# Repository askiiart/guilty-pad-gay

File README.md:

# GUILTY PAD -GAY-

Look this was gonna be normal but then the woke left made me add yuri

---

This is a macro pad which is designed with the [Guilty Pad XX Accent Core Plus Yuri](https://github.com/askiiart/guilty-pad-xx-accent-core-plus-yuri) in mind - can either act independently, or with the right firmware, could theoretically act as a very weird split keyboard. If you wanna get really crazy, it even has exposed i2c for expandability. For now it just includes very basic kmk firmware for testing.

## Bill of Materials

|Name                 |Quantity needed|MOQ|Price |Quantity to order|Link                                                           |Total   |
|---------------------|---------------|---|------|-----------------|---------------------------------------------------------------|--------|
|Xiao nRF52840        |1              |1  |9.99  |1                |<https://www.seeedstudio.com/Seeed-XIAO-BLE-nRF52840-p-5201.html>|9.99    |
|903090 lipo          |1              |1  |11.69 |1                |<https://www.aliexpress.us/item/3256809116041100.html>           |11.69   |
|AO3400A              |1              |20 |0.0214|20               |<https://www.lcsc.com/product-detail/C49195711.html>             |0.428   |
|AO3401A              |1              |20 |0.0321|20               |<https://www.lcsc.com/product-detail/C347476.html>               |0.642   |
|1N5819WS             |8              |100|0.0107|100              |<https://www.lcsc.com/product-detail/C191023.html>               |1.07    |
|74LV1T08GW-TP        |1              |10 |0.0609|10               |<https://www.lcsc.com/product-detail/C42460230.html>             |0.609   |
|TPS613222ADBVR       |1              |5  |0.1574|5                |<https://www.lcsc.com/product-detail/C2071163.html>              |0.787   |
|Inductor             |1              |5  |0.1508|5                |<https://www.lcsc.com/product-detail/C17701271.html>             |0.754   |
|SK6803MINI-E         |6              |10 |0.085 |10               |<https://www.lcsc.com/product-detail/C5242955.html>              |0.85    |
|22uF cap             |1              |20 |0.0354|20               |<https://www.lcsc.com/product-detail/C577040.html>               |0.708   |
|2M resistor          |1              |10 |0.0468|10               |<https://www.lcsc.com/product-detail/C2984387.html>              |0.468   |
|820k resistor        |2              |20 |0.0499|20               |<https://www.lcsc.com/product-detail/C865663.html>               |0.998   |
|                     |               |   |      |                 |                                                               |        |
|                     |               |   |      |                 |                                                               |        |
|seeed studio shipping|               |   |      |                 |                                                               |5.46    |
|LCSC shipping        |               |   |      |                 |                                                               |11.31   |
|                     |               |   |      |                 |                                                               |        |
|                     |               |   |      |                 |                                                               |        |
|Subtotal             |               |   |      |                 |                                                               |45.764  |
|Total                |               |   |      |                 |                                                               |49.53953|

## Art

- [bridget](https://danbooru.donmai.us/posts/10037913)
- [mayburi](https://danbooru.donmai.us/posts/10155469)
- [testament](https://x.com/kujikawaii/status/1534858361476358144)
- [elphelt](https://static.wikia.nocookie.net/guilty-gear/images/4/44/Elphelt_Guilty_Gear_Strive.png/revision/latest?cb=20240501125741) (from the elphelt fandom page)
- [other mayburi](https://danbooru.donmai.us/posts/9990984)

## Notes

- You can swap out the SK6803s for SK6812s, just keep in mind to account for them obviously being much brighter, and SK6803s have better color at low brightness.
- Clone recursively

## Assembly

Just solder the components as is obvious, then the case just slides together - it should be able to stay together on its own just fine, but it can also be glued or welded lightly if needed.

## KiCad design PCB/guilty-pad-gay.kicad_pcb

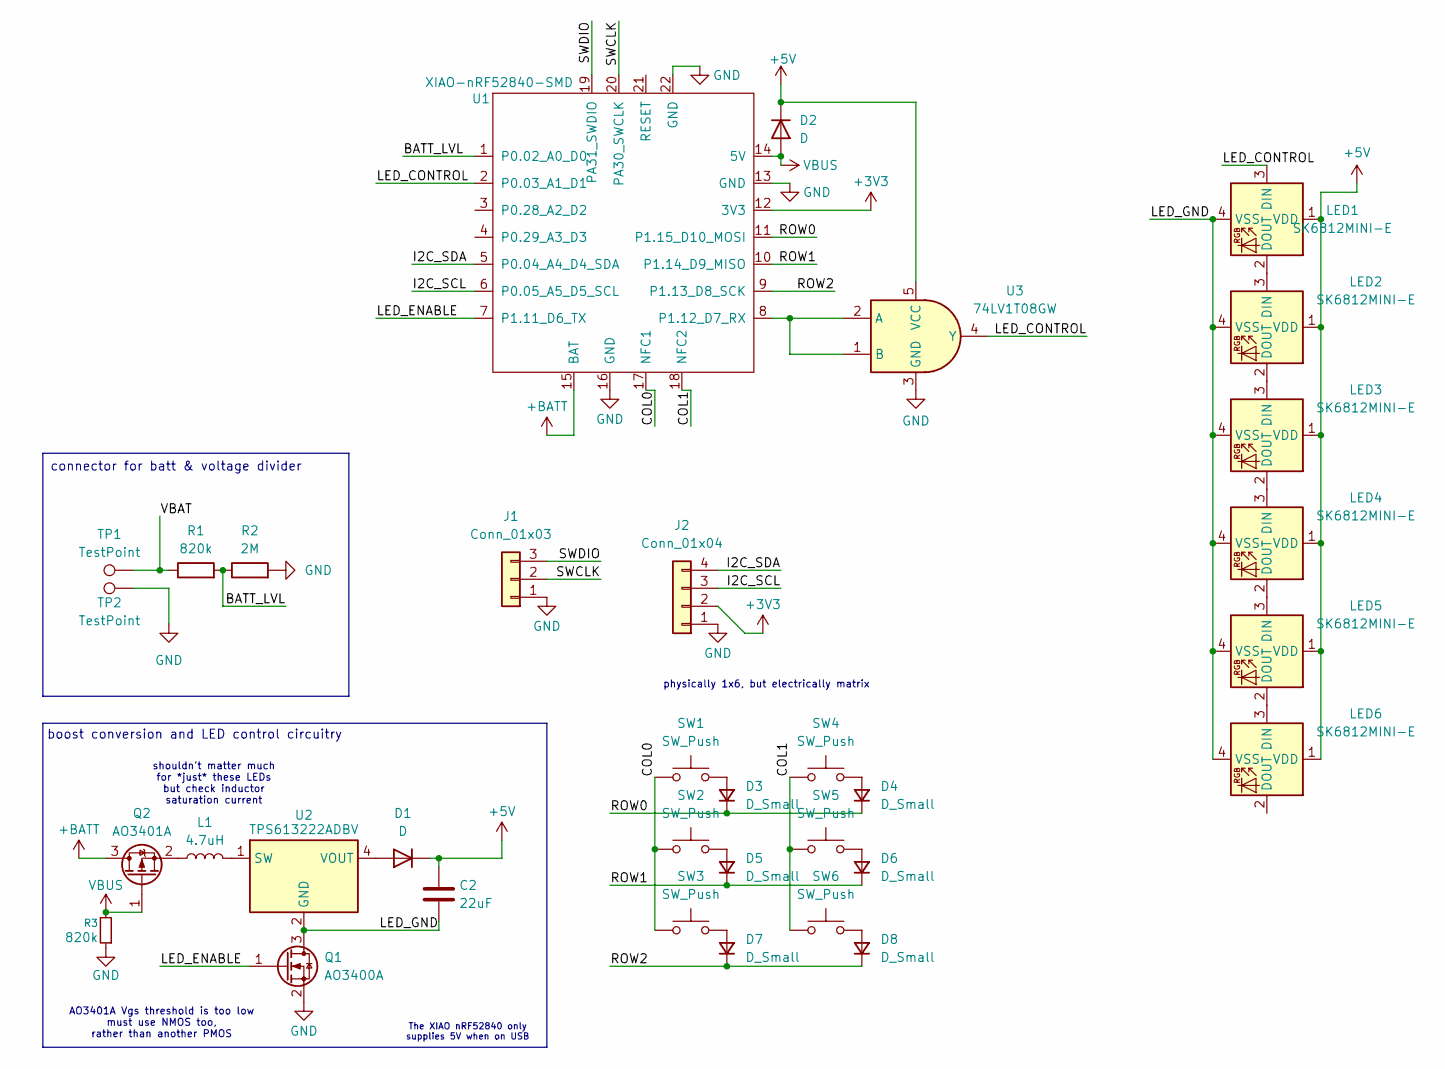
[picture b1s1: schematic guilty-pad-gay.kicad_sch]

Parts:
C2: 22uF; C_0603_1608Metric_Pad1.08x0.95mm_HandSolder
D1, D2: D; D_SOD-323_HandSoldering
D3, D4, D5, D6, D7, D8: D_Small; D_SOD-323_HandSoldering
J1: Conn_01x03; JST_GH_SM03B-GHS-TB_1x03-1MP_P1.25mm_Horizontal
J2: Conn_01x04; JST_GH_SM04B-GHS-TB_1x04-1MP_P1.25mm_Horizontal
L1: 4.7uH; L_1210_3225Metric_Pad1.42x2.65mm_HandSolder
LED1, LED2, LED3, LED4, LED5, LED6: SK6812MINI-E; LED_6028R
Q1: AO3400A; SOT-23
Q2: AO3401A; SOT-23
R1, R3: 820k; R_0805_2012Metric_Pad1.20x1.40mm_HandSolder
R2: 2M; R_0805_2012Metric_Pad1.20x1.40mm_HandSolder
SW1, SW2, SW3, SW4, SW5, SW6: SW_Push; SW_Cherry_MX_1.00u_PCB
TP1, TP2: TestPoint; TestPoint_Pad_2.0x2.0mm
U1: XIAO-nRF52840-SMD
U2: TPS613222ADBV; SOT-23-5
U3: 74LV1T08GW; SOT-353_SC-70-5

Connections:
+3V3: J2.2, U1.12 (3V3)
+5V: C2.2, D1.1 (K), D2.1 (K), LED1.1 (VDD), LED2.1 (VDD), LED3.1 (VDD), LED4.1 (VDD), LED5.1 (VDD), LED6.1 (VDD), U3.5 (VCC)
+BATT: Q2.3 (D), U1.15 (BAT)
/BATT_LVL: R1.2, R2.1, U1.1 (P0.02_A0_D0)
/COL0: SW1.1, SW2.1, SW3.1, U1.17 (NFC1)
/COL1: SW4.1, SW5.1, SW6.1, U1.18 (NFC2)
/I2C_SCL: J2.3, U1.6 (P0.05_A5_D5_SCL)
/I2C_SDA: J2.4, U1.5 (P0.04_A4_D4_SDA)
/LED_CONTROL: LED1.3 (DIN), U1.2 (P0.03_A1_D1), U3.4 (Y)
/LED_ENABLE: Q1.1 (G), U1.7 (P1.11_D6_TX)
/LED_GND: C2.1, LED1.4 (VSS), LED2.4 (VSS), LED3.4 (VSS), LED4.4 (VSS), LED5.4 (VSS), LED6.4 (VSS), Q1.3 (D), U2.2 (GND)
/ROW0: D3.1 (K), D4.1 (K), U1.11 (P1.15_D10_MOSI)
/ROW1: D5.1 (K), D6.1 (K), U1.10 (P1.14_D9_MISO)
/ROW2: D7.1 (K), D8.1 (K), U1.9 (P1.13_D8_SCK)
/SWCLK: J1.2, U1.20 (PA30_SWCLK)
/SWDIO: J1.3, U1.19 (PA31_SWDIO)
/VBAT: R1.1, TP1.1 (1_1)
GND: J1.1, J2.1, Q1.2 (S), R2.2, R3.1, TP2.1 (1_1), U1.13 (GND), U1.16 (GND), U1.22 (GND), U3.3 (GND)
unnamed: D1.2 (A), U2.4 (VOUT)
unnamed: D3.2 (A), SW1.2
unnamed: D4.2 (A), SW4.2
unnamed: D5.2 (A), SW2.2
unnamed: D6.2 (A), SW5.2
unnamed: D7.2 (A), SW3.2
unnamed: D8.2 (A), SW6.2
unnamed: LED1.2 (DOUT), LED2.3 (DIN)
unnamed: LED2.2 (DOUT), LED3.3 (DIN)
unnamed: LED3.2 (DOUT), LED4.3 (DIN)
unnamed: LED4.2 (DOUT), LED5.3 (DIN)
unnamed: LED5.2 (DOUT), LED6.3 (DIN)
unnamed: L1.1, Q2.2 (S)
unnamed: U1.8 (P1.12_D7_RX), U3.1 (B), U3.2 (A)
unnamed: L1.2, U2.1 (SW)
VBUS: D2.2 (A), Q2.1 (G), R3.2, U1.14 (5V)

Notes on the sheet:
physically 1x6, but electrically matrix
shouldn't matter much for *just* these LEDs but check inductor saturation current
boost conversion and LED control circuitry
AO3401A Vgs threshold is too low must use NMOS too, rather than another PMOS
connector for batt & voltage divider
The XIAO nRF52840 only supplies 5V when on USB

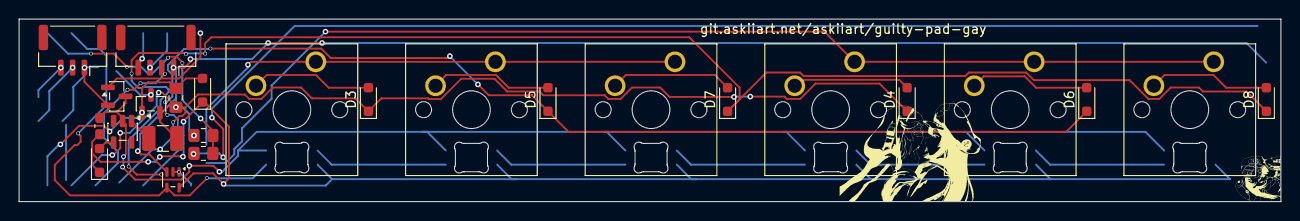
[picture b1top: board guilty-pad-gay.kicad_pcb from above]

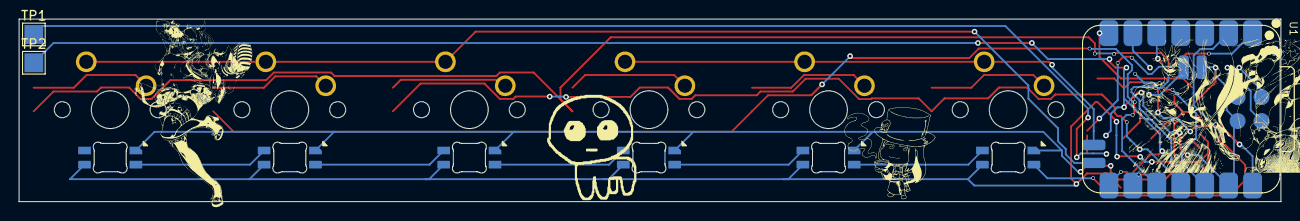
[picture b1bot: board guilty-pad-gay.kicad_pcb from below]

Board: 2 copper layers, 133.8 x 19.3 mm, 34 parts (9 on the bottom side), 34 nets.

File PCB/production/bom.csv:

Designator,Footprint,Quantity,Value,LCSC Part #
C2,0603,1,22uF,
"D1, D2",D_SOD-323_HandSoldering,2,D,
"D3, D4, D5, D6, D7, D8",D_SOD-323_HandSoldering,6,D_Small,
J1,JST_GH_SM03B-GHS-TB_1x03-1MP_P1.25mm_Horizontal,1,Conn_01x03,
J2,JST_GH_SM04B-GHS-TB_1x04-1MP_P1.25mm_Horizontal,1,Conn_01x04,
L1,1210,1,4.7uH,
"LED1, LED2, LED3, LED4, LED5, LED6",LED_6028R,6,SK6812MINI-E,
Q1,SOT-23,1,AO3400A,
Q2,SOT-23,1,AO3401A,
"R1, R3",0805,2,806k,
R2,0805,1,2M,
"SW1, SW2, SW3, SW4, SW5, SW6",SW_Cherry_MX_1.00u_PCB,6,SW_Push,
"TP1, TP2",TestPoint_Pad_2.0x2.0mm,2,TestPoint,
U1,XIAO-nRF52840-SMD,1,XIAO-nRF52840-SMD,
U2,SOT-23-5,1,TPS613222ADBV,
U3,SOT-353_SC-70-5,1,74LV1T08GW,

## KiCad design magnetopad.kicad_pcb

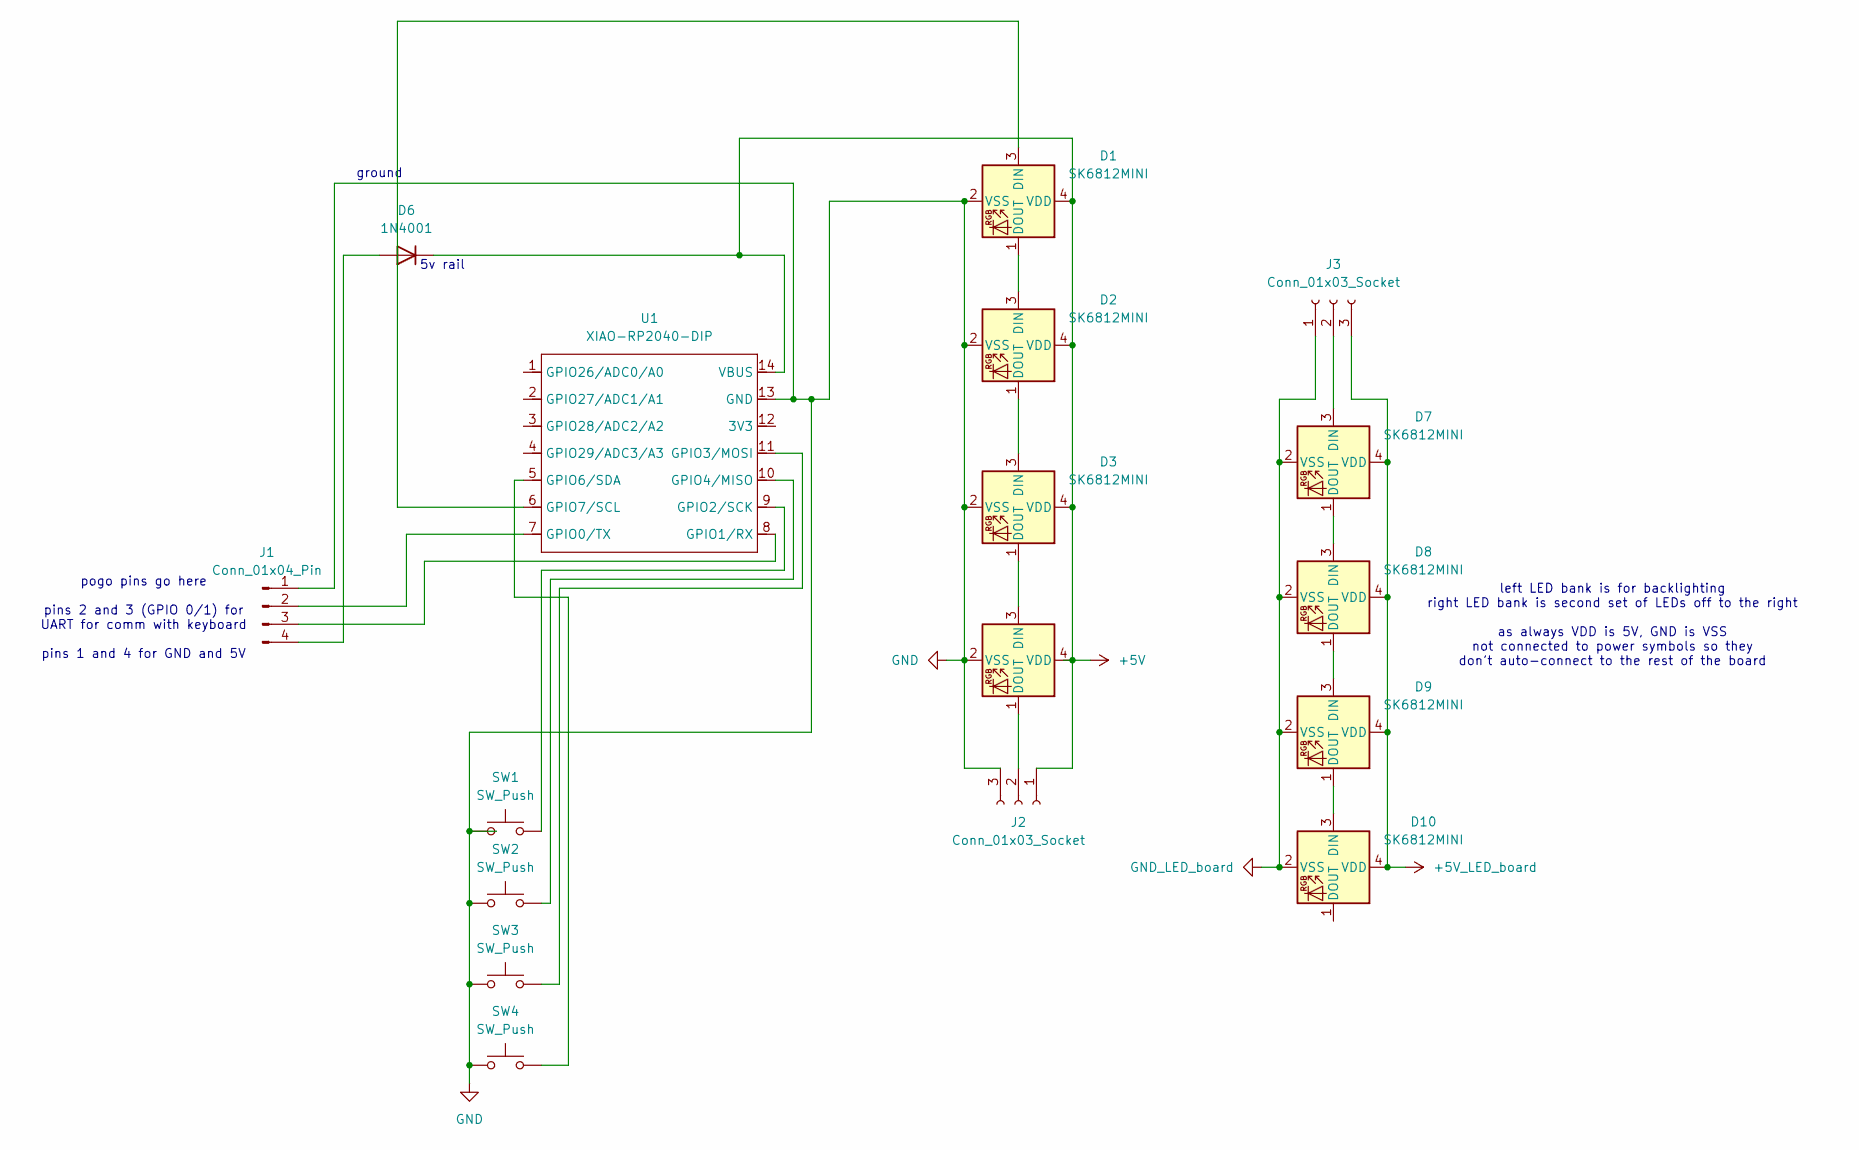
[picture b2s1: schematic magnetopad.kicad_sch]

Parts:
D1, D2, D3, D4, D7, D8, D9, D10: SK6812MINI; LED_SK6812MINI_PLCC4_3.5x3.5mm_P1.75mm
D6: 1N4001; D_DO-41_SOD81_P10.16mm_Horizontal
J1: Conn_01x04_Pin; PinHeader_1x04_P2.54mm_Vertical
J2, J3: Conn_01x03_Socket; PinSocket_1x03_P2.54mm_Vertical
SW1, SW2, SW3, SW4: SW_Push; SW_Cherry_MX_1.00u_PCB
U1: XIAO-RP2040-DIP

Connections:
+5V: D1.4 (VDD), D2.4 (VDD), D3.4 (VDD), D4.4 (VDD), D6.1 (K), J2.1, U1.14 (VBUS)
+5V_LED_board: D7.4 (VDD), D8.4 (VDD), D9.4 (VDD), D10.4 (VDD), J3.3
GND: D1.2 (VSS), D2.2 (VSS), D3.2 (VSS), D4.2 (VSS), J1.1, J2.3, SW1.1, SW2.1, SW3.1, SW4.1, U1.13 (GND)
GND_LED_board: D7.2 (VSS), D8.2 (VSS), D9.2 (VSS), D10.2 (VSS), J3.1
unnamed: D1.3 (DIN), U1.6 (GPIO7/SCL)
unnamed: D1.1 (DOUT), D2.3 (DIN)
unnamed: D2.1 (DOUT), D3.3 (DIN)
unnamed: D3.1 (DOUT), D4.3 (DIN)
unnamed: D4.1 (DOUT), J2.2
unnamed: D6.2 (A), J1.4
unnamed: D7.3 (DIN), J3.2
unnamed: D7.1 (DOUT), D8.3 (DIN)
unnamed: D8.1 (DOUT), D9.3 (DIN)
unnamed: D9.1 (DOUT), D10.3 (DIN)
unnamed: J1.2, U1.7 (GPIO0/TX)
unnamed: J1.3, U1.8 (GPIO1/RX)
unnamed: SW1.2, U1.9 (GPIO2/SCK)
unnamed: SW3.2, U1.11 (GPIO3/MOSI)
unnamed: SW2.2, U1.10 (GPIO4/MISO)
unnamed: SW4.2, U1.5 (GPIO6/SDA)

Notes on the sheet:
pogo pins go here pins 2 and 3 (GPIO 0/1) for UART for comm with keyboard pins 1 and 4 for GND and 5V
left LED bank is for backlighting right LED bank is second set of LEDs off to the right as always VDD is 5V, GND is VSS not connected to power symbols so they don't auto-connect to the rest of the board
5v rail
ground

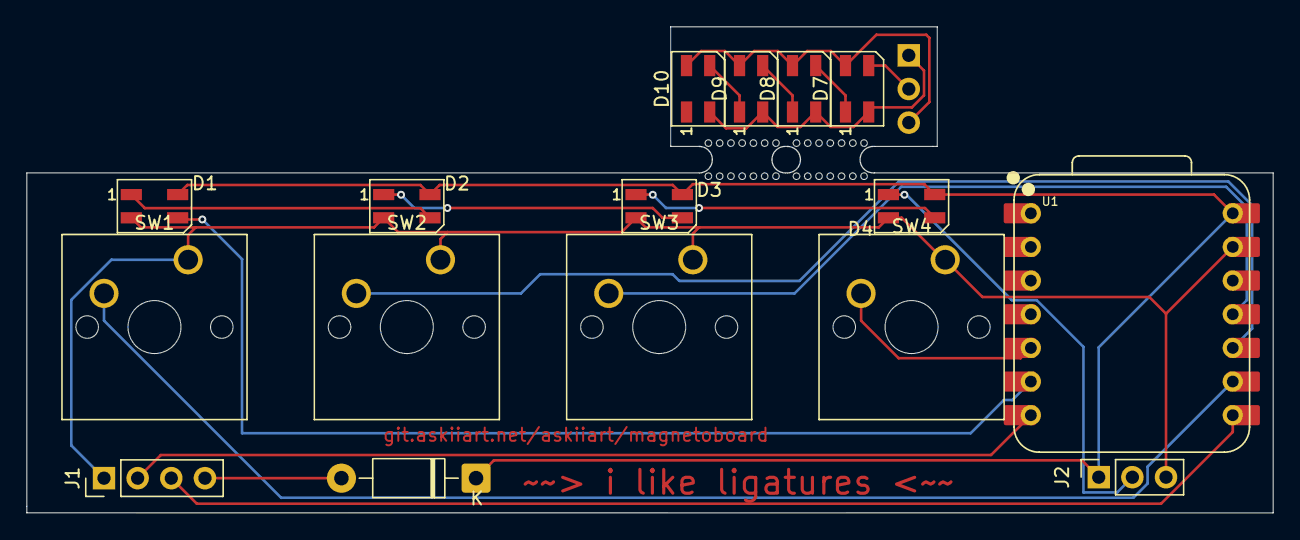
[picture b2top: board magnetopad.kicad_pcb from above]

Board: 2 copper layers, 94.0 x 36.6 mm, 17 parts (1 on the bottom side), 20 nets.

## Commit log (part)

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2025-11-19 initial version - routed and passes DRC
2025-11-19 update README, add custom lib with socket for pogo assembly
2025-11-21 - update to use the right LEDs (SK6812MINI-E) (added marbastlib for that) - redo the board a bit so it actually lines up with the keycap grid decently - add art :3
2025-11-21 just move yuri around a bit
2025-11-21 updated README with yuri credit
2025-11-24 - add case - rename
2025-11-25 wild guess at firmware copied from claude lol
    i'll make something actually decent (and with the serial stuff) later
2025-11-29 switch to nrf, add boost converter stuff for running LEDs off battery, and update the README
2025-11-29 update case, minor pcb updates. should be ready to submit
2025-11-29 swap out the capacitor for a bigger one - can use it for both this and the full-size board
2025-11-30 swap to 5V and use level shifter - much more sane
2025-11-30 i forgor to swap out text, that's all
2026-06-17 look idek i just want this in git
2026-06-22 look idr what's different but uh yeag i'm committing
2026-06-28 update with routed and parts and stuffs
2026-06-28 add BOM and update image
2026-06-28 add new cad
2026-06-29 add holes for keys
2026-06-30 add assembled cad
2026-06-30 remove temporary BOM
